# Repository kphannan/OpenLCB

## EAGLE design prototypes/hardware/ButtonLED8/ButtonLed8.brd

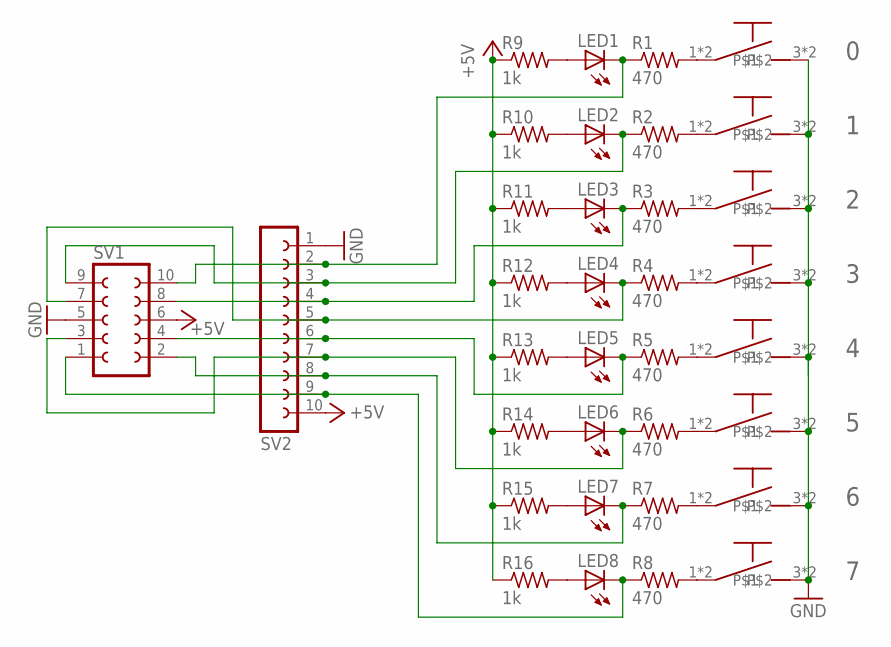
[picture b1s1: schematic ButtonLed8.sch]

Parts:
LED1, LED2, LED3, LED4, LED5, LED6, LED7, LED8: LED3MM
R1, R2, R3, R4, R5, R6, R7, R8: 470; 0204/7
R9, R10, R11, R12, R13, R14, R15, R16: 1k; 0204/7
SV1: FE05-2
SV2: FE10-1; FE10
U$1, U$2, U$3, U$4, U$5, U$6, U$7, U$8: BUTTON; SPARKFUN_TACTILE-PTH

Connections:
+5V: R9.1, R10.1, R11.1, R12.1, R13.1, R14.1, R15.1, R16.1, SV1.6, SV2.10
GND: SV1.5, SV2.1, U$1.3, U$1.4, U$2.3, U$2.4, U$3.3, U$3.4, U$4.3, U$4.4, U$5.3, U$5.4, U$6.3, U$6.4, U$7.3, U$7.4, U$8.3, U$8.4
unnamed: R1.2, U$1.1, U$1.2
unnamed: R2.2, U$2.1, U$2.2
unnamed: R4.2, U$4.1, U$4.2
unnamed: R5.2, U$5.1, U$5.2
unnamed: R6.2, U$6.1, U$6.2
unnamed: R7.2, U$7.1, U$7.2
unnamed: R8.2, U$8.1, U$8.2
unnamed: LED1.K (C), R1.1, SV1.10, SV2.2
unnamed: LED3.K (C), R3.1, SV1.8, SV2.4
unnamed: LED4.K (C), R4.1, SV1.7, SV2.5
unnamed: LED5.K (C), R5.1, SV1.4, SV2.6
unnamed: LED6.K (C), R6.1, SV1.3, SV2.7
unnamed: LED7.K (C), R7.1, SV1.2, SV2.8
unnamed: LED8.K (C), R8.1, SV1.1, SV2.9
unnamed: R3.2, U$3.1, U$3.2
unnamed: LED1.A, R9.2
unnamed: LED2.A, R10.2
unnamed: LED3.A, R11.2
unnamed: LED4.A, R12.2
unnamed: LED5.A, R13.2
unnamed: LED6.A, R14.2
unnamed: LED7.A, R15.2
unnamed: LED8.A, R16.2
unnamed: LED2.K (C), R2.1, SV1.9, SV2.3

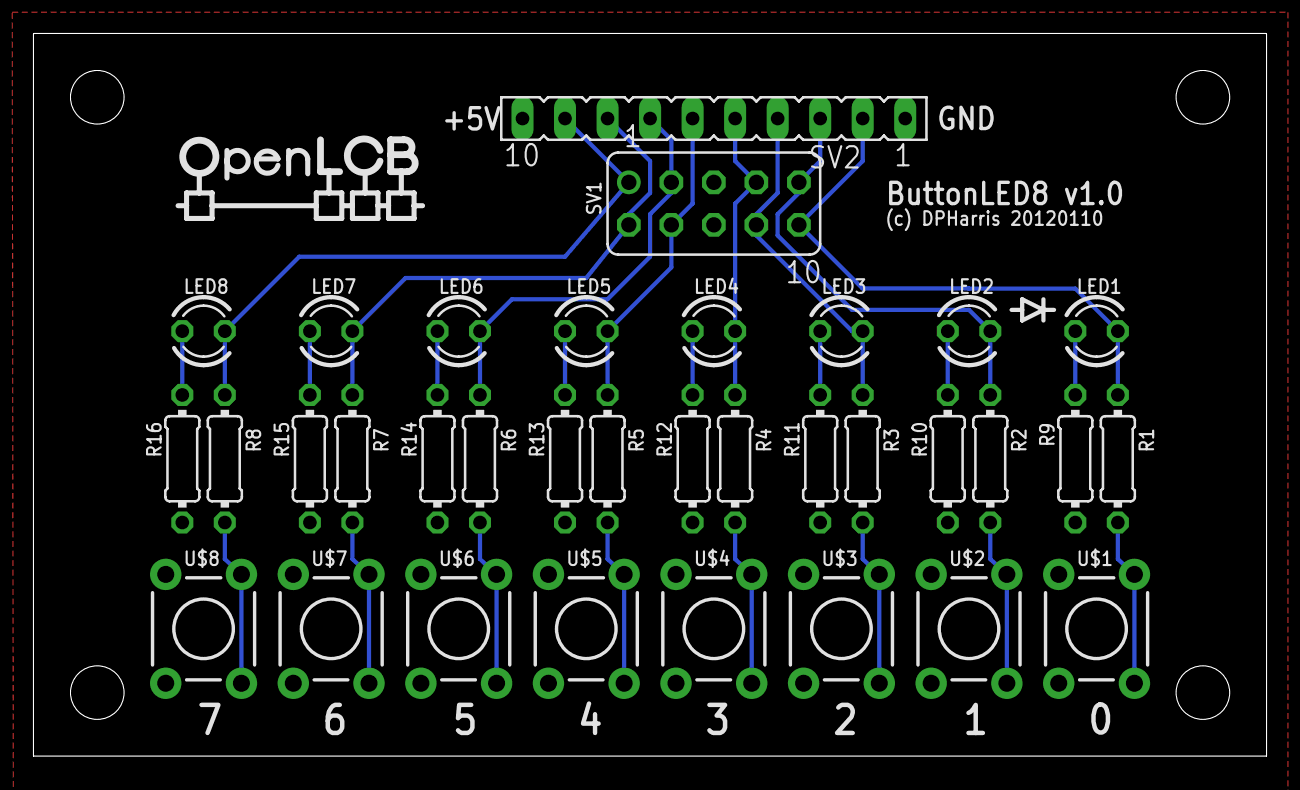
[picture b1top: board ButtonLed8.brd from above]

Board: 2 copper layers, 73.7 x 43.2 mm, 35 parts (0 on the bottom side), 26 nets.

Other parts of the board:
U$9: OPENLCB_LOGOV

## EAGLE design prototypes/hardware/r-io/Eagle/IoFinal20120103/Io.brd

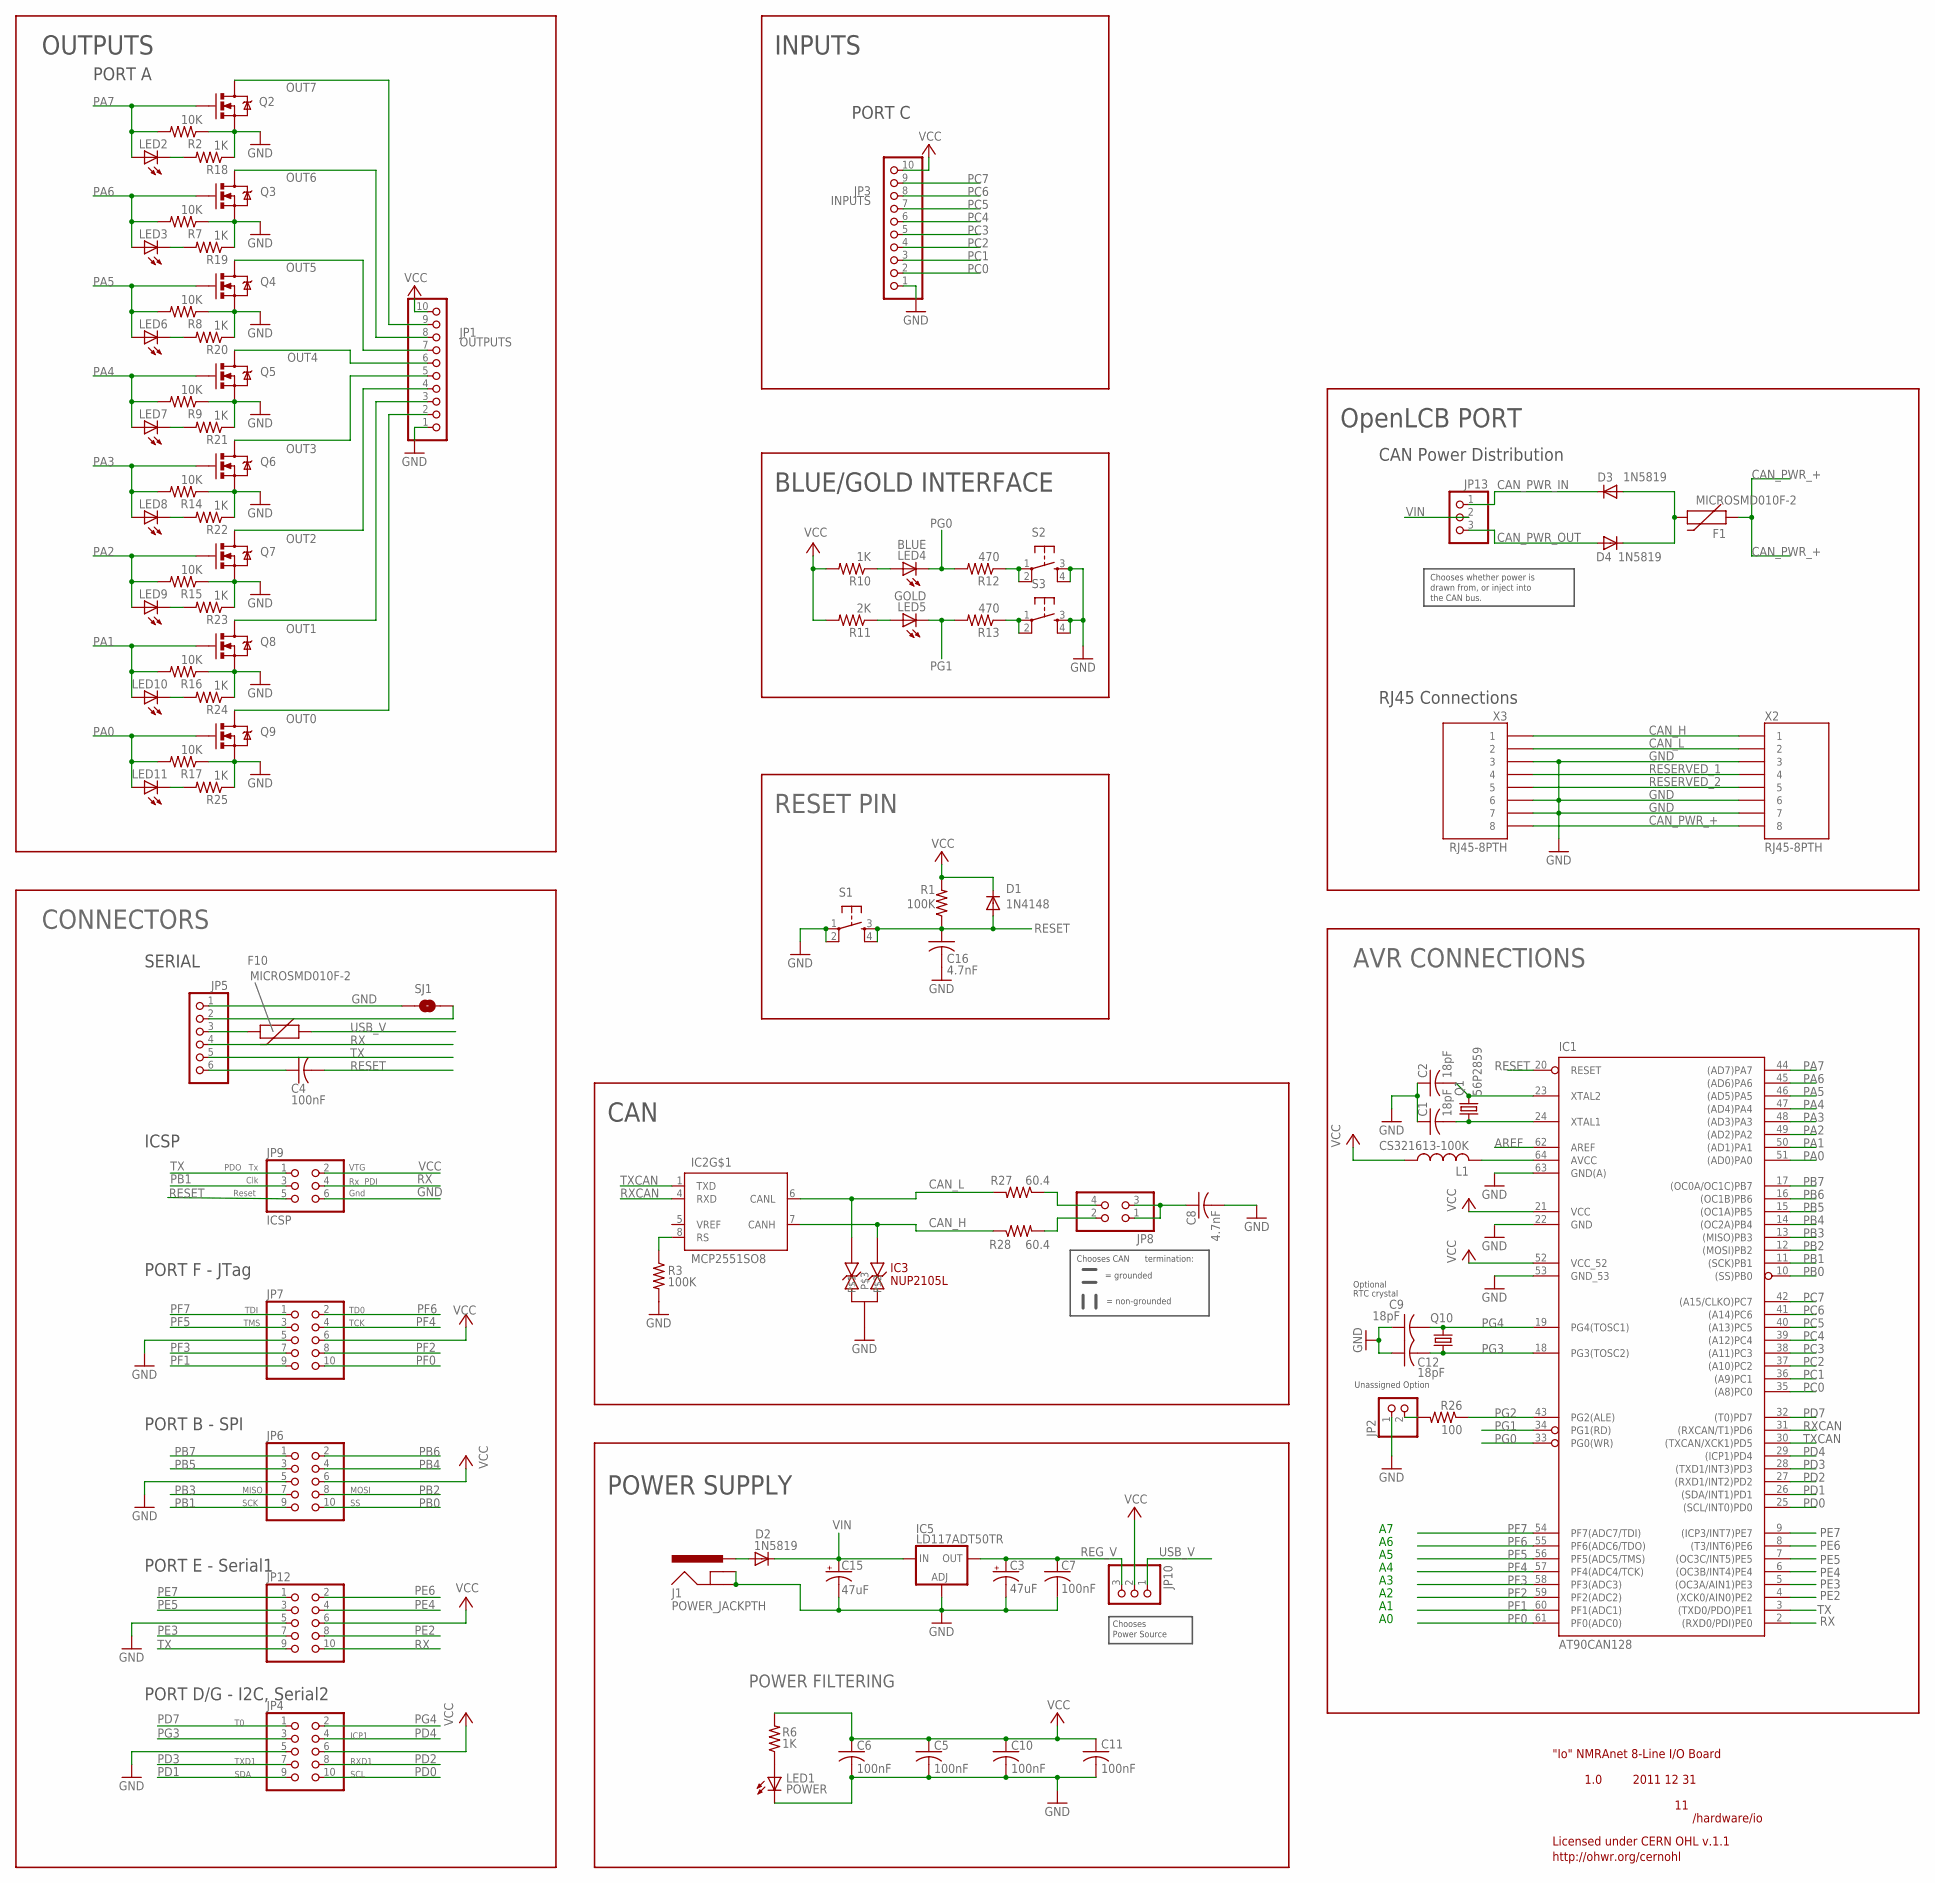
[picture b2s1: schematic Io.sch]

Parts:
C1, C2, C9, C12: 18pF; C1206
C3, C15: 47uF; UD-6,3X5,8_NICHICON
C4, C5, C6, C7, C10, C11: 100nF; C1206
C8, C16: 4.7nF; C1206
D1: 1N4148; SOD123
D2, D3, D4: 1N5819; SMA-DIODE
F1, F10: MICROSMD010F-2; PTC-1206
IC1: AT90CAN128; TQFP64
IC2: MCP2551SO8; SO08
IC3: NUP2105L; SOT-23
IC5: LD117ADT50TR; DPACK
J1: POWER_JACKPTH; POWER_JACK_PTH
JP1: OUTPUTS; 1X10
JP2: PINHD-1X2; 1X02
JP3: INPUTS; 1X10
JP4, JP6, JP7, JP12: 2X5_HEADERSHROUDED; 2X5_SHROUD
JP5: PINHD-1X6; 1X06
JP8: PINHD-2X2; 2X02
JP9: ICSP; 2X03
JP10, JP13: PINHD-1X3; 1X03
L1: CS321613-100K; L3216C
LED1: POWER; CHIPLED_1206
LED2, LED3, LED6, LED7, LED8, LED9, LED10, LED11: LEDCHIPLED_1206; CHIPLED_1206
LED4: BLUE; CHIPLED_1206
LED5: GOLD; CHIPLED_1206
Q1: 56P2859; HC49/S
Q2, Q3, Q4, Q5, Q6, Q7, Q8, Q9: PMV56XN; SOT23-3
Q10: CRYSTALTC26V; TC26V
R1, R3: 100K; R1206
R2, R7, R8, R9, R14, R15, R16, R17: 10K; R1206
R6, R10, R18, R19, R20, R21, R22, R23, R24, R25: 1K; R1206
R11: 2K; R1206
R12, R13: 470; R1206
R26: 100; R1206
R27, R28: 60.4; R1206
S1, S2, S3: TAC_SWITCHPTH; TACTILE-PTH
SJ1: SOLDERJUMPERTRACE; SJ_2S-TRACE
X2, X3: RJ45-8PTH; RJ45-8

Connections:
AREF: IC1.62 (AREF)
CAN_H: IC2.7 (CANH), IC3.2, R28.1, X2.1, X3.1
CAN_L: IC2.6 (CANL), IC3.1, R27.2, X2.2, X3.2
CAN_PWR_+: F1.1, X2.8, X3.8
CAN_PWR_IN: D3.C, JP13.1
CAN_PWR_OUT: D4.A, JP13.3
GND: C1.1, C2.1, C3.-, C5.2, C6.2, C7.2, C8.2, C9.1, C10.2, C11.2, C12.1, C15.-, C16.2, IC1.22 (GND), IC1.53 (GND_53), IC1.63 (GND(A)), IC2.2 (GND), IC3.3, IC5.1 (ADJ), J1.GND, J1.GNDBREAK, JP1.1, JP2.1, JP3.1, JP4.5, JP5.1, JP6.5, JP7.5, JP9.6, JP12.5, LED1.C, Q2.2 (S), Q3.2 (S), Q4.2 (S), Q5.2 (S), Q6.2 (S), Q7.2 (S), Q8.2 (S), Q9.2 (S), R2.1, R3.2, R7.1, R8.1, R9.1, R14.1, R15.1, R16.1, R17.1, R18.1, R19.1, R20.1, R21.1, R22.1, R23.1, R24.1, R25.1, S1.1, S1.2, S2.3, S2.4, S3.3, S3.4, SJ1.2, X2.3, X2.6, X2.7, X3.3, X3.6, X3.7
unnamed: JP8.2, R28.2
unnamed: JP8.4, R27.1
unnamed: LED4.A, R10.1
unnamed: LED5.A, R11.1
unnamed: IC2.8 (RS), R3.1
unnamed: R12.1, S2.1, S2.2
unnamed: F10.2, JP5.3
unnamed: LED1.A, R6.1
unnamed: D2.A, J1.PWR
unnamed: C1.2, IC1.24 (XTAL1), Q1.1
unnamed: R13.1, S3.1, S3.2
unnamed: LED10.C, R24.2
unnamed: LED9.C, R23.2
unnamed: LED8.C, R22.2
unnamed: D3.A, D4.C, F1.2
unnamed: LED7.C, R21.2
unnamed: LED6.C, R20.2
unnamed: LED3.C, R19.2
unnamed: LED2.C, R18.2
unnamed: LED11.C, R25.2
unnamed: IC1.64 (AVCC), L1.2
unnamed: JP5.2, SJ1.1
unnamed: C8.1, JP8.1, JP8.3
unnamed: JP2.2, R26.2
unnamed: C4.1, JP5.6
OUT0: JP1.2, Q9.3 (D)
OUT1: JP1.3, Q8.3 (D)
OUT2: JP1.4, Q7.3 (D)
OUT3: JP1.5, Q6.3 (D)
OUT4: JP1.6, Q5.3 (D)
OUT5: JP1.7, Q4.3 (D)
OUT6: JP1.8, Q3.3 (D)
OUT7: JP1.9, Q2.3 (D)
PA0: IC1.51 ((AD0)PA0), LED11.A, Q9.1 (G), R17.2
PA1: IC1.50 ((AD1)PA1), LED10.A, Q8.1 (G), R16.2
PA2: IC1.49 ((AD2)PA2), LED9.A, Q7.1 (G), R15.2
PA3: IC1.48 ((AD3)PA3), LED8.A, Q6.1 (G), R14.2
PA4: IC1.47 ((AD4)PA4), LED7.A, Q5.1 (G), R9.2
PA5: IC1.46 ((AD5)PA5), LED6.A, Q4.1 (G), R8.2
PA6: IC1.45 ((AD6)PA6), LED3.A, Q3.1 (G), R7.2
PA7: IC1.44 ((AD7)PA7), LED2.A, Q2.1 (G), R2.2
PB0: IC1.10 ((SS)PB0), JP6.10
PB1: IC1.11 ((SCK)PB1), JP6.9, JP9.3
PB2: IC1.12 ((MOSI)PB2), JP6.8
PB3: IC1.13 ((MISO)PB3), JP6.7
PB4: IC1.14 ((OC2A)PB4), JP6.4
PB5: IC1.15 ((OC1A)PB5), JP6.3
PB6: IC1.16 ((OC1B)PB6), JP6.2
PB7: IC1.17 ((OC0A/OC1C)PB7), JP6.1
PC0: IC1.35 ((A8)PC0), JP3.2
PC1: IC1.36 ((A9)PC1), JP3.3
PC2: IC1.37 ((A10)PC2), JP3.4
PC3: IC1.38 ((A11)PC3), JP3.5
PC4: IC1.39 ((A12)PC4), JP3.6
PC5: IC1.40 ((A13)PC5), JP3.7
PC6: IC1.41 ((A14)PC6), JP3.8
PC7: IC1.42 ((A15/CLKO)PC7), JP3.9
PD0: IC1.25 ((SCL/INT0)PD0), JP4.10
PD1: IC1.26 ((SDA/INT1)PD1), JP4.9
PD2: IC1.27 ((RXD1/INT2)PD2), JP4.8
PD3: IC1.28 ((TXD1/INT3)PD3), JP4.7
PD4: IC1.29 ((ICP1)PD4), JP4.4
PD7: IC1.32 ((T0)PD7), JP4.1
PE2: IC1.4 ((XCK0/AIN0)PE2), JP12.8
PE3: IC1.5 ((OC3A/AIN1)PE3), JP12.7
PE4: IC1.6 ((OC3B/INT4)PE4), JP12.4
PE5: IC1.7 ((OC3C/INT5)PE5), JP12.3
PE6: IC1.8 ((T3/INT6)PE6), JP12.2
PE7: IC1.9 ((ICP3/INT7)PE7), JP12.1
PF0: IC1.61 (PF0(ADC0)), JP7.10
PF1: IC1.60 (PF1(ADC1)), JP7.9
PF2: IC1.59 (PF2(ADC2)), JP7.8
PF3: IC1.58 (PF3(ADC3)), JP7.7
PF4: IC1.57 (PF4(ADC4/TCK)), JP7.4
PF5: IC1.56 (PF5(ADC5/TMS)), JP7.3
PF6: IC1.55 (PF6(ADC6/TDO)), JP7.2
PF7: IC1.54 (PF7(ADC7/TDI)), JP7.1
PG0: IC1.33 (PG0(WR)), LED4.C, R12.2
PG1: IC1.34 (PG1(RD)), LED5.C, R13.2
PG2: IC1.43 (PG2(ALE)), R26.1
PG3: C12.2, IC1.18 (PG3(TOSC2)), JP4.3, Q10.1
PG4: C9.2, IC1.19 (PG4(TOSC1)), JP4.2, Q10.2
REG_V: C3.+, C7.1, IC5.4 (OUT), JP10.3
RESERVED_1: X2.4, X3.4
RESERVED_2: X2.5, X3.5
RESET: C4.2, C16.1, D1.A, IC1.20 (RESET), JP9.5, R1.1, S1.3, S1.4
RX: IC1.2 ((RXD0/PDI)PE0), JP5.4, JP9.4, JP12.10
RXCAN: IC1.31 ((RXCAN/T1)PD6), IC2.4 (RXD)
TX: IC1.3 ((TXD0/PDO)PE1), JP5.5, JP9.1, JP12.9
TXCAN: IC1.30 ((TXCAN/XCK1)PD5), IC2.1 (TXD)
USB_V: F10.1, JP10.1
VCC: C5.1, C6.1, C10.1, C11.1, D1.C, IC1.21 (VCC), IC1.52 (VCC_52), IC2.3 (VCC), JP1.10, JP3.10, JP4.6, JP6.6, JP7.6, JP9.2, JP10.2, JP12.6, L1.1, R1.2, R6.2, R10.2, R11.2
VIN: C15.+, D2.C, IC5.3 (IN), JP13.2
XTAL1: C2.2, IC1.23 (XTAL2), Q1.2

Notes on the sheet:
POWER SUPPLY
OpenLCB PORT
CAN
POWER FILTERING
RESET PIN
AVR CONNECTIONS
"Io" NMRAnet 8-Line I/O Board
2011 12 31
1.0
/hardware/io
BLUE/GOLD INTERFACE
Licensed under CERN OHL v.1.1
http://ohwr.org/cernohl
VTG
Clk
Gnd
Reset
TDI
TD0
TMS
TCK
SCL
SDA
RXD1
TXD1
ICP1
SCK
MOSI
MISO
PDO
PDI
INPUTS
OUTPUTS
CONNECTORS
PORT F - JTag
PORT B - SPI
PORT E - Serial1
PORT D/G - I2C, Serial2
PORT A
PORT C

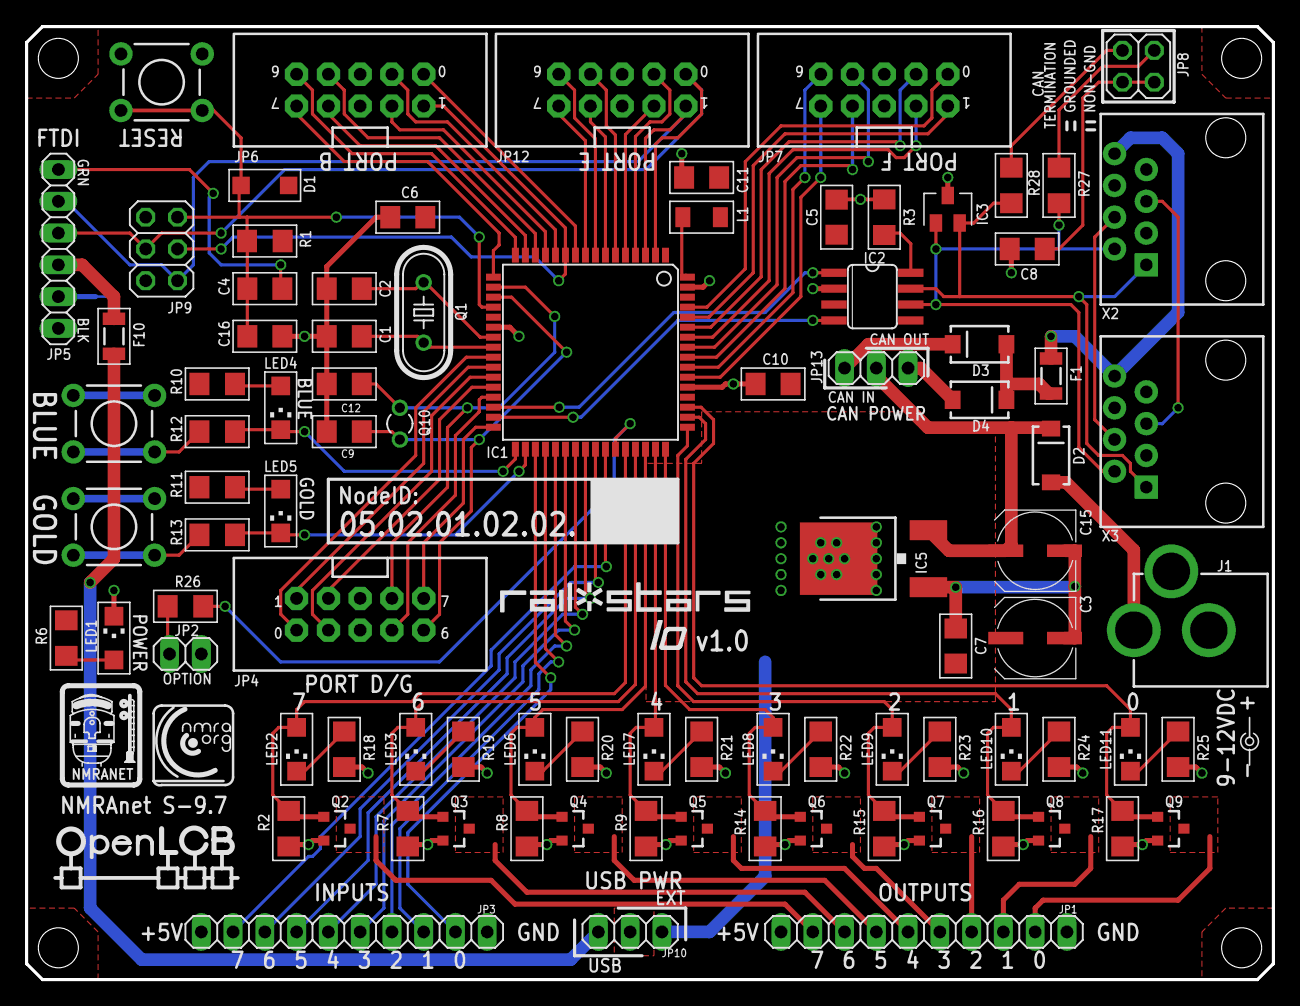
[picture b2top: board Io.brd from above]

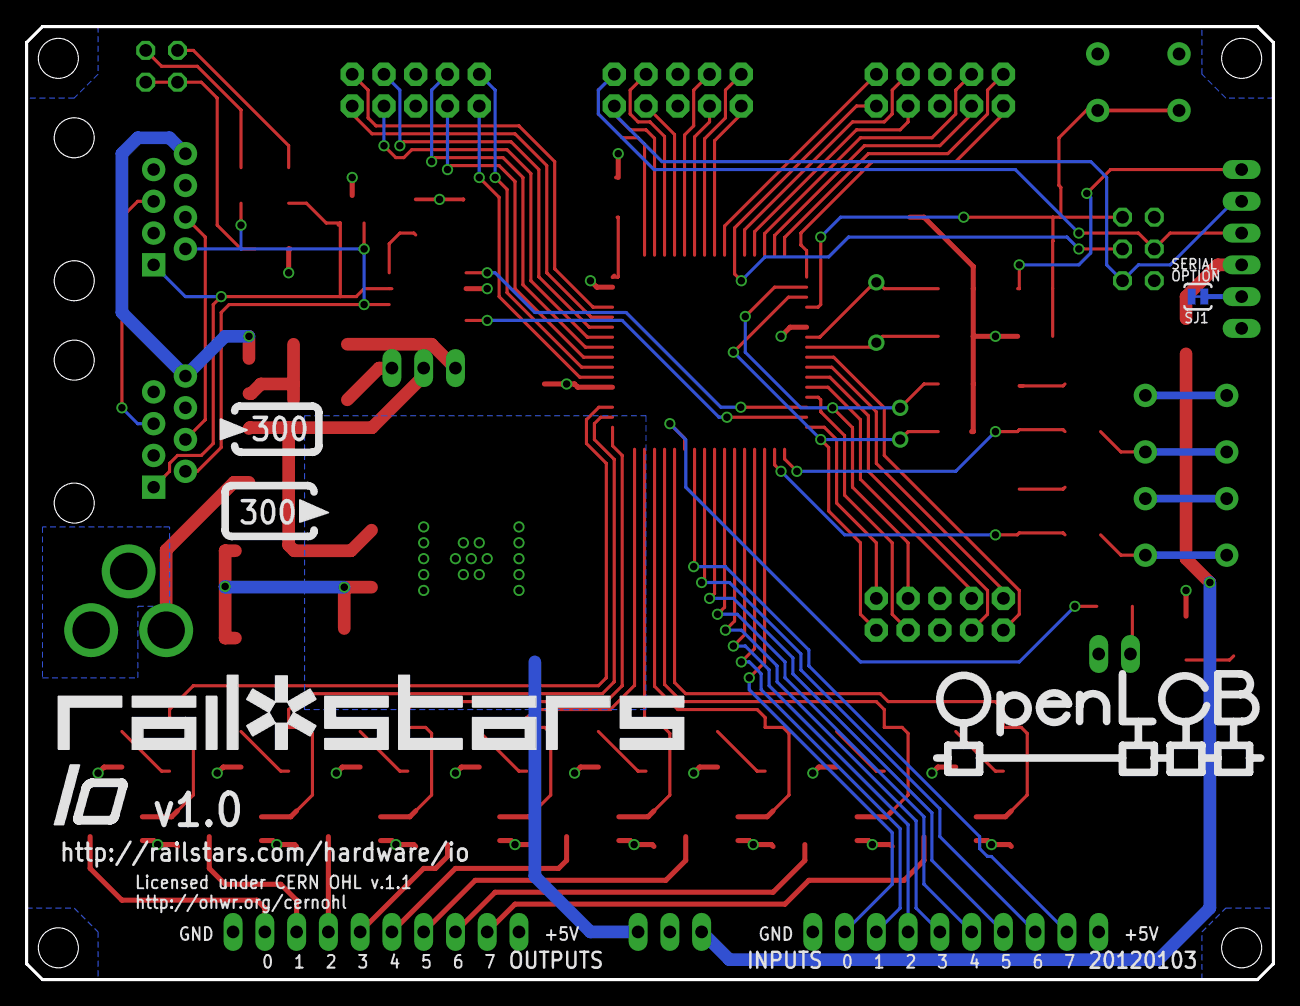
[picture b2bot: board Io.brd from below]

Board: 2 copper layers, 99.7 x 76.2 mm, 101 parts (2 on the bottom side), 100 nets.

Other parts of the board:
U$1: RAILSTARS_LOGO_IO_V
U$2: ARTIFICIAL_SCIENCE_RAILSTARS_50MM_INV
U$3: RAILSTARS_1IN
U$4: OPENLCB_NMRANET_LOGO_MED
U$7: RAILSTARS_LOGO_IO_LARGE_V_INV
U$8: CURRENT_DRAWV_INV
U$9: OPENLCB_LOGOV
U$10: NMRA_ORG_SMALL
U$11: CURRENT_PROVIDEV_INV
U$13: OPENLCB_OPENLCB_LOGO_LARGE

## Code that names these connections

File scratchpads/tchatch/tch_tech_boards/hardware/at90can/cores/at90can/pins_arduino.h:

/*
  pins_arduino.h - Pin definition functions for Arduino
  Part of Arduino - http://www.arduino.cc/

  Copyright (c) 2007 David A. Mellis

  This library is free software; you can redistribute it and/or
  modify it under the terms of the GNU Lesser General Public
  License as published by the Free Software Foundation; either
  version 2.1 of the License, or (at your option) any later version.

  This library is distributed in the hope that it will be useful,
  but WITHOUT ANY WARRANTY; without even the implied warranty of
  MERCHANTABILITY or FITNESS FOR A PARTICULAR PURPOSE.  See the GNU
  Lesser General Public License for more details.

  You should have received a copy of the GNU Lesser General
  Public License along with this library; if not, write to the
  Free Software Foundation, Inc., 59 Temple Place, Suite 330,
  Boston, MA  02111-1307  USA

  $Id: wiring.h 249 2007-02-03 16:52:51Z mellis $
*/

#ifndef Pins_Arduino_h
#define Pins_Arduino_h

#include <avr/pgmspace.h>

#ifndef PCICR
#define PCICE EICR
#endif
#ifndef PCMSK
#define PCMSK EIMSK
#endif

#define NUM_DIGITAL_PINS            50
#define NUM_ANALOG_INPUTS           8

#define analogInputToDigitalPin(p)  ((p < 8) ? (p) + 40 : -1)

/* not gonna bother with PWM */
#define digitalPinHasPWM(p)         (0)

const static uint8_t SS   = 8;
const static uint8_t MOSI = 10;
const static uint8_t MISO = 11;
const static uint8_t SCK  = 9;

const static uint8_t SDA = 25;
const static uint8_t SCL = 24;
const static uint8_t LED_BUILTIN = 48;
const static uint8_t BLUE = 48;
const static uint8_t GOLD = 49;

const static uint8_t A0 = 40;
const static uint8_t A1 = 41;
const static uint8_t A2 = 42;
const static uint8_t A3 = 43;
const static uint8_t A4 = 44;
const static uint8_t A5 = 45;
const static uint8_t A6 = 46;
const static uint8_t A7 = 47;

//PC interrupts are not available on the AT90CAN128
#define digitalPinToPCICR(p)    (0)
#define digitalPinToPCICRbit(p) (1)
#define digitalPinToPCMSK(p)    ((uint8_t *)0)
#define digitalPinToPCMSKbit(p) (p)

#ifdef ARDUINO_MAIN

// these arrays map port names (e.g. port B) to the
// appropriate addresses for various functions (e.g. reading
// and writing)
const uint16_t PROGMEM port_to_mode_PGM[] = {
	NOT_A_PORT,
	(uint16_t) &DDRA,
	(uint16_t) &DDRB,
	(uint16_t) &DDRC,
	(uint16_t) &DDRD,
	(uint16_t) &DDRE,
	(uint16_t) &DDRF,
};

const uint16_t PROGMEM port_to_output_PGM[] = {
	NOT_A_PORT,
	(uint16_t) &PORTA,
	(uint16_t) &PORTB,
	(uint16_t) &PORTC,
	(uint16_t) &PORTD,
	(uint16_t) &PORTE,
	(uint16_t) &PORTF,
};

const uint16_t PROGMEM port_to_input_PGM[] = {
	NOT_A_PORT,
	(uint16_t) &PINA,
	(uint16_t) &PINB,
	(uint16_t) &PINC,
	(uint16_t) &PIND,
	(uint16_t) &PINE,
	(uint16_t) &PINF,
};

const uint8_t PROGMEM digital_pin_to_port_PGM[] = {
	PA, /* 0 OUTPUTS */
	PA,
	PA,
	PA,
	PA,
	PA,
	PA,
	PA, /* 7 */
	PB, /* 8 */
	PB,
	PB,
	PB,
	PB,
	PB,
	PB,
	PB, /* 15 */
	PC, /* 16 INPUTS*/
	PC, 
	PC,
	PC,
	PC,
	PC,
	PC,
	PC, /* 23 */
	PD, /* 24 */
	PD, 
	PD,
	PD,
	PD,
	PG, /* PD5 is CAN: Sub in PG3 here */
	PG, /* PD6 is CAN: Sub in PG4 here */
	PD, /* 31 */
	PE, /* 32 */
	PE, 
	PE,
	PE,
	PE,
	PE,
	PE,
	PE, /* 39 */
	PF, /* 40 */
	PF, 
	PF,
	PF,
	PF,
	PF,
	PF,
	PF, /* 47 */
	PG, /* 48 BLUE */
	PG, /* 49 GOLD */
};

const uint8_t PROGMEM digital_pin_to_bit_mask_PGM[] = {
	_BV(0), /* 0, port A */
	_BV(1), /* 1, port A */
	_BV(2), /* 2, port A */
	_BV(3), /* 3, port A */
	_BV(4), /* 4, port A */
	_BV(5), /* 5, port A */
	_BV(6), /* 6, port A */
	_BV(7), /* 7, port A */
	
	_BV(0), /* 0, port B */
	_BV(1), /* 1, port B */
	_BV(2), /* 2, port B */
	_BV(3), /* 3, port B */
	_BV(4), /* 4, port B */
	_BV(5), /* 5, port B */
	_BV(6), /* 6, port B */
	_BV(7), /* 7, port B */
	
	_BV(0), /* 0, port C */
	_BV(1), /* 1, port C */
	_BV(2), /* 2, port C */
	_BV(3), /* 3, port C */
	_BV(4), /* 4, port C */
	_BV(5), /* 5, port C */
	_BV(6), /* 6, port C */
	_BV(7), /* 7, port C */
	
	_BV(0), /* 0, port D */
	_BV(1), /* 1, port D */
	_BV(2), /* 2, port D */
	_BV(3), /* 3, port D */
	_BV(4), /* 4, port D */
	_BV(3), /* 3, port G */
	_BV(4), /* 4, port G */
	_BV(7), /* 7, port D */
	
	_BV(0), /* 0, port E */
	_BV(1), /* 1, port E */
	_BV(2), /* 2, port E */
	_BV(3), /* 3, port E */
	_BV(4), /* 4, port E */
	_BV(5), /* 5, port E */
	_BV(6), /* 6, port E */
	_BV(7), /* 7, port E */

	_BV(0), /* 0, port F */
	_BV(1), /* 1, port F */
	_BV(2), /* 2, port F */
	_BV(3), /* 3, port F */
	_BV(4), /* 4, port F */
	_BV(5), /* 5, port F */
	_BV(6), /* 6, port F */
	_BV(7), /* 7, port F */
	
	_BV(0), /* 0, port G BLUE */
	_BV(1), /* 1, port G GOLD */
};


/* Just not gonna mess with it! */
const uint8_t PROGMEM digital_pin_to_timer_PGM[] = {
	NOT_ON_TIMER, /* 0 */
	NOT_ON_TIMER, /* 1 */
	NOT_ON_TIMER,	  /* 2 */
	NOT_ON_TIMER,      /* 3 */
	NOT_ON_TIMER, 	  /* 4 */
	NOT_ON_TIMER,      /* 5 */
	NOT_ON_TIMER,      /* 6 */
	NOT_ON_TIMER, /* 7 */
	NOT_ON_TIMER, /* 8 */
	NOT_ON_TIMER,      /* 9 */
	NOT_ON_TIMER, /* 10 */
	NOT_ON_TIMER, /* 11 */
	NOT_ON_TIMER, /* 12 */
	NOT_ON_TIMER, /* 13 */
	NOT_ON_TIMER, /* 14 */
	NOT_ON_TIMER, /* 15 */
	NOT_ON_TIMER, /* 16 */
	NOT_ON_TIMER, /* 17 */
	NOT_ON_TIMER, /* 18 */
	NOT_ON_TIMER, /* 19 */
	NOT_ON_TIMER, /* 20 */
	NOT_ON_TIMER, /* 21 */
	NOT_ON_TIMER, /* 22 */
	NOT_ON_TIMER, /* 23 */
	NOT_ON_TIMER, /* 24 */
	NOT_ON_TIMER, /* 25 */
};

#endif

#endif

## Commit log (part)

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2014-07-23 add protocols
2014-07-23 update to current content
2014-07-23 fix typo
2014-07-24 - PIC32 CAN library apparently working correctly, proof is in connecting it to the network...
2014-07-25 add new json blocks
2014-07-28 - Updates to PIC32 and big dsPIC projects
2014-09-23 Edits and some small progress on a few specs
2014-10-29 - More work on the PIC32 Ethernet to CAN Bridge
2014-10-31 - Fixed bugs in the PIC32 Ethernet/CAN bridge project - Updated library to work with the high performance PIC18F parts with CAN modules. The CAN library is not functional yet.
2014-11-02 - Cleaned up Ethernet Bridge Code
2014-11-02 - Working Ethernet bridge, committing before I get hit with another bolt of lightning taking out my hardware
2014-11-24 - Added the Simple Train Node Information protocol
2014-12-23 Adds two copies of the GenStreamTransportWN named as S and TN, respectively. Starts editing the cover page of the S document to start to look like a Standard.
2014-12-23 Add definitions section to the stream standard; minor cleanup in the initiate request/reply messages.
2014-12-29 Finishes touching up the messages, defined states, starts on interactions.
2014-12-31 Adds a proposal for error codes to the general message network standard draft.
2015-02-07 - EventTransportS and TN edited
2015-02-07 - Corrected errors and updates in the EventIdAllocation Table and pdf file - Interim changes in the datagramS
2015-02-07 dph files
2015-02-07 ready for review
2015-02-07 rename GenEventId* to EventIdentifiers*
2015-02-07 new organization for CDI
2015-02-07 dph files - minor change
2015-02-08 work in progress
2015-02-08 - Datagram S and TN ready for review and renamed without the GenXXX
2015-02-08 dph error codes
2015-02-08 additional updates
2015-02-08 - Fixed Priorities for Traction and Button MTIs
2015-02-08 - Added list for actions that must be looked at based on decisions make during documentation blitz for the 2015 NMRA submittal
2015-02-08 minor tweeks
2015-02-08 rename GenSimpleNodeInfo* to SimpleNodeInformation*.
2015-02-08 add clarification suggested by David
2015-02-08 add version; tidy; extension element
2015-02-08 cleans up todos in the SNIP standard.
2015-02-08 Final checkup on the SNIP S doc.
2015-02-09 ready for final review
2015-02-09 fix heading
2015-02-09 fix footer
2015-02-09 MessageNetwork ready for review
2015-02-09 fixed Makefile
2015-02-09 - Fixed issues with EventTransportS - First upload of Configuration Memory. Still have a couple of notes to resolve with Bob
2015-02-09 Writes the TN for the SNIP protocol.
2015-02-10 SimpleNodeInformation review comments
2015-02-10 fix comment
2015-02-11 fixes up canframetransfer. S and TN.
2015-02-11 - Update based on Balazs's markups.
2015-02-12 adds a test file
2015-02-12 Finishes writeup for CDI standard.
2015-02-13 - Update font
2015-02-13 error tab
2015-02-13 error codes updated
2015-02-13 MsgNetwk pdfs
2015-02-13 minor change in format
2015-02-13 formating
2015-02-13 Fixes a mistake in the cointrol frame overview table: makes the AME frame's data content Optional Full Node ID.
2015-02-14 Clarify AME usage
2015-02-14 Add logo back
2015-02-14 fix witch to which
2015-02-14 Glossary edits accepted, minor change to MsgNet
2015-02-14 CommonInformationTN review
2015-02-14 Diagram for CANFrame
2015-02-14 CDIS comments by dph
2015-02-15 added review comments for DatagramTransportS and applied those comments to the document
2015-02-15 minor changes
2015-02-15 added review comments for CanFrameTransferS and applied those comments to the document
2015-02-15 added review comments for CanFrameTransferTN and applied those comments to the document
2015-02-15 CANPhysicalS&TN accepted, pdfs generated
2015-02-15 EventTransport accepted, pdfs generated
2015-02-15 renames GenCdi{S,TN} to CommonInformation{S,TN}
2015-02-15 Adds an 'nmra' target to compile all nmra files to pdf.
2015-02-15 Moves CanFrameTransfer from drafts to staging
2015-02-15 Finishes can frame transport S and TN, adds pdf, moves image.
2015-02-15 Moves SNIP from draft to staging.
2015-02-15 rmeoves obsolete pdfs
2015-02-15 finalizes eventidentifiers s and tn.
2015-02-15 Moves glossary to staging.
2015-02-15 Moves CommonInformation to staging
2015-02-15 accepts the last change.
2015-02-15 finalizes eventtransport S and TN
2015-02-15 finalizes messagenetwork.
2015-02-15 balazs edits installed
2015-02-15 removed watermark and marked Adpted
2015-02-15 Moves unique id to staging
2015-02-15 removes obsolete files
2015-02-15 fixes review comments.
2015-02-15 minor edit
2015-02-15 ticks off completed comments.
2015-02-15 commits diffs.
2015-02-16 Edit to MsgNet, add FrontLeaf and ExecutiveSummary
2015-02-16 Comments for CDITN
2015-02-16 Changes from Jims comments
2015-02-16 fixes a typo
2015-02-16 Moves CDI S and TN to staging
2015-02-16 regeneratesfrontleaf.pdf
2015-02-16 Moves datagram to staging.
2015-02-17 Moves datagram images. Finalizes datagram S and TN
2015-02-17 Accepts changes
2015-02-17 Finalizes memory config
2015-02-17 ifinalizes can physical
2015-02-17 updates to MemoryConfiguration
2015-02-17 finalized the new version.
2015-02-17 Error codes made specific
2015-02-17 added NMRA Layout Command Control (LCC) cover pages
2015-02-17 Adds compilation makefile to wrap standards in nmra format. Copies a snapshot of the staged standards.
2015-02-17 finalizes yet another version.
2015-02-17 Refreshes all source PDFs.
2015-02-17 Minor fixes to executive summary
2015-02-17 updates filename generation
2015-02-17 updates covers to use arial font instead of helvetica.
2015-02-17 Makes the 'l' uppercase to 'L' in the example code.
2015-02-18 Changed Standard to Technical Note
2015-02-18 removes obsolete version. Current is now in staging.
2015-02-18 Fixes TOC
2015-02-18 Adds a link to the issue list
2015-02-21 Moves comments files to separate directories
2015-02-21 Moves some drafts to obsolete: ACDI has been berged into ConfigurationDescriptionInformationS. PIP has been merged into MessageNetwork and made required.
2015-02-21 Removes orphan PDFs. These were branched from their original versions (Gen*) when moved to staging.
2015-02-23 Changes the makefile to generate different filenames. Regenerates the LCC submission files.
2015-02-24 Changed the position of the S & TN in the document Label in the title block table from 9.7.x.x-S/TN to S/TN-9.7.x.x
2015-03-01 changed file name formatting to match the text on the document title block as in: S-9.7.x.x and TN-9.7.x.x
2015-05-29 - Fixed bits for the multi part message in the TCP S and TN
2015-06-20 JDOM 2
2015-06-20 jar files as of today, made with Java 1.8
2015-07-12 generalize the CDI test for demo/development purposes
2015-07-13 - Radical reworking of the original /trunk/spec folder to try to clean it up and get it in sync with the LCC specs (naming conventions, drafts, organizing where the Allocation tables are, etc.)
2015-07-13 - Started to update the index.html file for the specs
2015-08-01 new class based on EventIdTextField
2015-08-08 - New Parts added to PCB Artist Library
2015-08-16 support generating UML-illustrated JavaDoc
2015-08-16 improve JavaDoc
2015-08-16 test sequential operations
2015-08-16 TCP and status update. Note: This project may now be orphaned. Not clear what the future will bring. If you don't see updates here after a reasonable time, perhaps it's been moved to another group, b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
2015-08-16 Adding doc re Note: This project may now be orphaned. Not clear what the future will bring. If you don't see updates here after a reasonable time, perhaps it's been moved to another group, but it may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
2015-08-18 Added float format. Created a new folder, as I assume that the previous schema is used already.
2015-09-08 Fixed a bug in datagram acknowledgement handling that was leaking threads.
    Previously if datagram traffic was present on the bus that JMRI is listening to, JMRI would incorrectly spawn a thread for each datagram sent between other nodes. The datagram acknowledgement handler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
    Steps to reproduce:
    1) start two JMRIs and connect to the same bus. These can run on different computers, or on the same computer with two CANUSB adapters, or connect to the same TCP hub.
    2) Add a third node to the bus (e.g. a RailStars IO node would be fine)
    3) from JMRI-A open the CDI condifurat
2015-09-08 patch by Bob Jacobsen: "Fixes timing issue in memory write replies."
    This patch includes several changes:
    - fixes a bug in the datagram transmit handler that could cause the transmit Memo pointer to be lost. Previously if the transmit callback would immediately send a new datagram, the new datagram would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
    - adds scaffolding for support in Memory Config protocol writes that may send back a (possibly delayed) return datagram instead of just a success/failure to the write request datagram. The write resp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
    - extends unittests for datagram transmit Memo objects.
2015-09-08 Recompiles jar files after patches are applied.
2015-09-18 Adds firmware upgrade proposal to the SVN, to be discussed with the mailing list. Important: this is not a draft standard yet.
2015-09-19 Rolled OlcbBasicNode.ino to r3117, had been overwritten with xml.
2015-10-17 Updated documents based on peer reviewed feedback
2015-10-18 Responded to comments provided as peer reviewed feedback
2015-12-13 update CanPhysical with DCC signal use case for pins 4 & 5
2015-12-28 Adds a constructor that wraps any CanFrame into an OclbCanFrame.
2015-12-28 Adds abstract interfaces that is responsible for instantiating all standards-compliant components.
2015-12-28 Finishes implementing the state machine inside the NIDaAlgorithm for the local alias allocation. Fixes previous standard-incompliant behavior in the alias conflict handling. Implements all timer meth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
2015-12-28 Fixes bug in ToLong with negative-valued bytes.
2015-12-28 Simplifies inheritance relation of MimicNodeStore, removes unneeded MessageDecoder parent.
2015-12-28 Fixes nullptr crash on partial CAN messages.
2015-12-28 Adds gitignore file for gitsvn users.
2015-12-30 Updated links to TCH Technology
2016-01-01 Adds fake classes for testing with OlcbInterface objects.
2016-01-01 Renames TrainNode to RemoteTrainNode to better represent the intention of this class (as opposed to Node classes that act as a node on the bus).
2016-01-01 Implementing traction protocol messages: - adds new abstract message base class: AddressedPayloadMessage, with common handling for parsing and serializing. - adds MTI values for traction control/prox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
2016-01-01 Adds getters for service object inside the interface.
2016-01-01 Ensures that components get the messages in the order of their registration.
2016-01-01 Adds accessors for parsing the messages.
2016-01-01 Adds a set of utility classes that allow different components to agree upon a shared value, where updates can come from either ofthese components.
2016-01-01 Adds some log statements to traction throttle.
2016-01-02 CAN lib update
2016-01-03 Fixes incorrectly declared constructor.
2016-01-03 Adds simple set at current call.
2016-01-06 Fix Stream tests
2016-01-06 fix dashboard
2016-01-09 Adds interface accessor.
2016-01-09 Adds a release method.
2016-01-09 Adds differentiation of various producer identified and consumer identified messages by the Event State. Updates unit tests as well.
2016-01-09 Adds a gridconnect parser, formatter to the CAN package and tests for them.
2016-01-09 Adds mockito as test runner library dependency.
2016-01-09 Fixes parsing of can frame "identify event addressed". Adds error logging when the incoming CAN message is known but unhandled.
2016-01-10 updates to DCC signal usage of pins 4 & 5
2016-01-14 Fixes bug that the incoming CAN frames were not routed to the alias mapping object. Sends out an AME frame upon boot to initialize the alias mapping cache.
2016-01-14 Ensures that function values are queries only once during initial construction of the throttle.
2016-01-18 Missed commiting the IDE Library manager required file.
2016-01-18 Moved MsTimer2 library to olcb-MsTimer2-Library and added support for Arduino IDE Library Manager
2016-01-18 Updated library.properties to be more accurate.
2016-01-18 Moved MemoryFree library to olcb-MemoryFree-Library and added support for Arduino IDE Library Manager
2016-01-18 Fixed URL punctuation and author

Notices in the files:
prototypes/hardware/r-io/Eagle/IoFinal20120103/Io.brd:
Copyright (C) 2011 D.E. Goodman-Wilson
